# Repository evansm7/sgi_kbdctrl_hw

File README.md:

# SGI Indigo PS/2 keyboard/mouse adapter PCB

26 April 2026

This is the PCB companion to the [sgi_indigo_kbdctrl firmware](https://github.com/evansm7/sgi_indigo_kbdctrl) project. 

Has enough on board to be self-powered using the 8V from the Indigo, or can be built with a barrel jack to take 5VDC (which is probably nicer for the SGI).

Can be built with a dual/stacked PS/2 connector for keyboard/mouse in one footprint, or two one-socket connectors side by side.

# License

sgi_kbdctrl_hw is copyright 2016 Matt Evans.

This work is licensed under the Creative Commons Attribution-NonCommercial-ShareAlike 3.0 Unported License. To view a copy of this license, visit http://creativecommons.org/licenses/by-nc-sa/3.0/ or send a letter to Creative Commons, PO Box 1866, Mountain View, CA 94042, USA.

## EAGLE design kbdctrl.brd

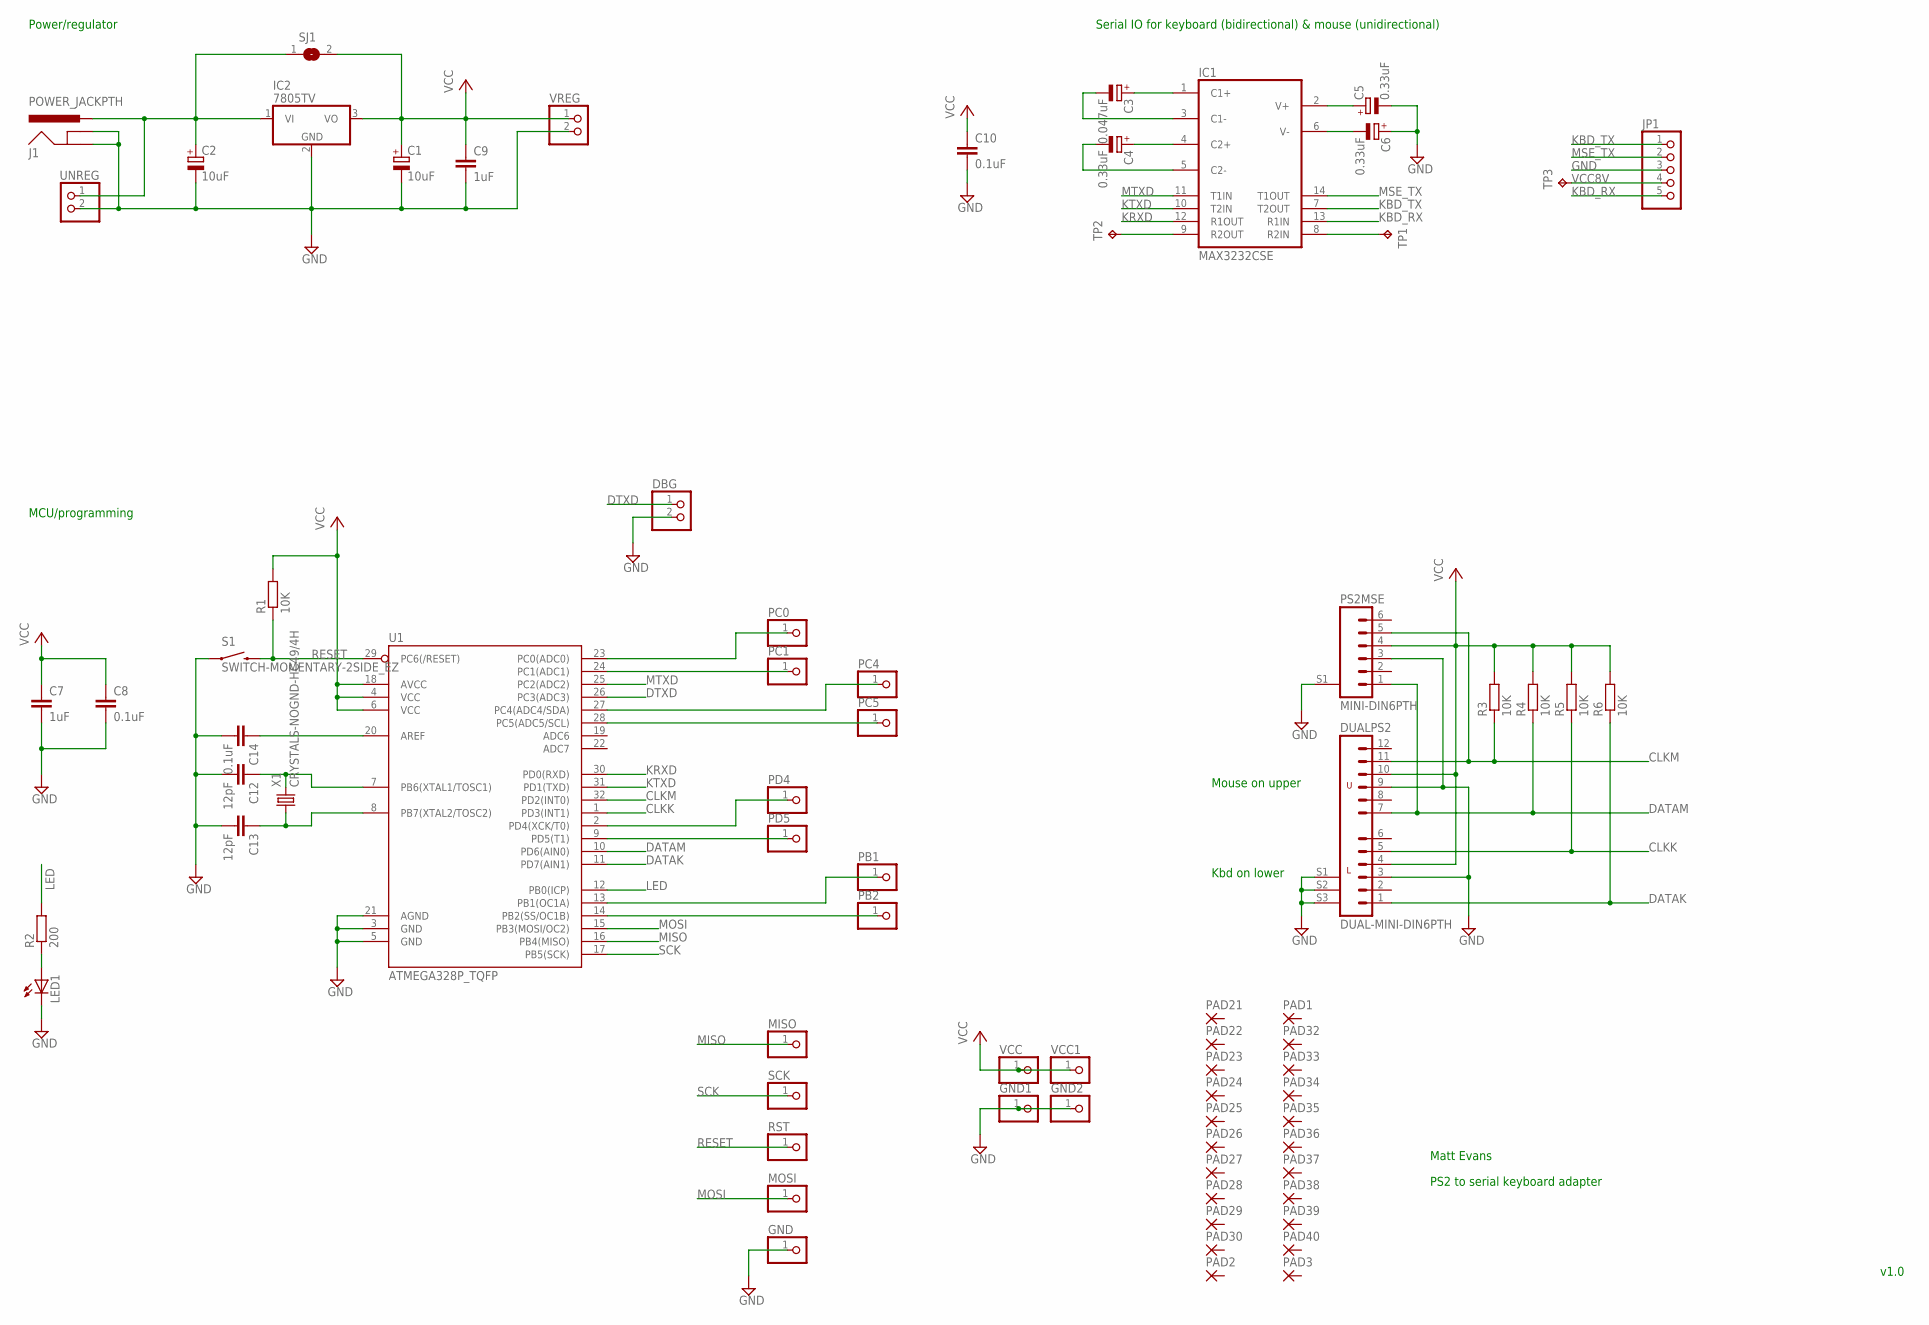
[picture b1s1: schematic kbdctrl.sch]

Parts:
C1, C2: 10uF; SMC_P
C3: 0.047uF; SMC_P
C4, C5, C6: 0.33uF; SMC_P
C7, C9: 1uF; C0805
C8, C10: 0.1uF; C0805
C12, C13: 12pF; C0603
C14: 0.1uF; C0603
DBG: PINHD-1X2; 1X02
DUALPS2: DUAL-MINI-DIN6PTH; DUAL-MINI-DIN6
GND, GND1, GND2: PINHD-1X1; 1X01
IC1: MAX3232CSE; SO16
IC2: 7805TV; TO220V
J1: POWER_JACKPTH; POWER_JACK_PTH
JP1: PINHD-1X5; 1X05
LED1: LEDSML0805; SML0805
MISO: PINHD-1X1; 1X01
MOSI: PINHD-1X1; 1X01
PAD1, PAD2, PAD3, PAD21, PAD22, PAD23, PAD24, PAD25, PAD26, PAD27, PAD28, PAD29, PAD30, PAD32, PAD33, PAD34, PAD35, PAD36, PAD37, PAD38, PAD39, PAD40: 1,6/0,9
PB1, PB2: PINHD-1X1; 1X01
PC0, PC1, PC4, PC5: PINHD-1X1; 1X01
PD4, PD5: PINHD-1X1; 1X01
PS2MSE: MINI-DIN6PTH; MINI-DIN6
R1, R3, R4, R5, R6: 10K; R0603
R2: 200; R0603
RST: PINHD-1X1; 1X01
S1: SWITCH-MOMENTARY-2SIDE_EZ; TACTILE-PTH-SIDEEZ
SCK: PINHD-1X1; 1X01
SJ1: SJ
TP1, TP2, TP3: TPTP09SQ; TP09SQ
U1: ATMEGA328P_TQFP; TQFP32-08
UNREG: PINHD-1X2; 1X02
VCC, VCC1: PINHD-1X1; 1X01
VREG: PINHD-1X2; 1X02
X1: CRYSTALS-NOGND-HC49/4H; HC49

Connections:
CLKK: DUALPS2.5, R5.1, U1.1 (PD3(INT1))
CLKM: DUALPS2.11, PS2MSE.5, R3.1, U1.32 (PD2(INT0))
DATAK: DUALPS2.1, R6.1, U1.11 (PD7(AIN1))
DATAM: DUALPS2.7, PS2MSE.1, R4.1, U1.10 (PD6(AIN0))
DTXD: DBG.1, U1.26 (PC3(ADC3))
GND: C1.-, C2.-, C5.-, C6.+, C7.2, C8.2, C9.2, C10.2, C12.2, C13.2, C14.2, DBG.2, DUALPS2.3, DUALPS2.9, DUALPS2.S1, DUALPS2.S2, DUALPS2.S3, GND.1, GND1.1, GND2.1, IC1.15 (GND), IC2.2 (GND), J1.GND, J1.GNDBREAK, JP1.3, LED1.C, PS2MSE.3, PS2MSE.S1, S1.1, U1.3 (GND), U1.5 (GND), U1.21 (AGND), UNREG.2, VREG.2
KBD_RX: IC1.13 (R1IN), JP1.5
KBD_TX: IC1.7 (T2OUT), JP1.1
KRXD: IC1.12 (R1OUT), U1.30 (PD0(RXD))
KTXD: IC1.10 (T2IN), U1.31 (PD1(TXD))
LED: R2.2, U1.12 (PB0(ICP))
MISO: MISO.1, U1.16 (PB4(MISO))
MOSI: MOSI.1, U1.15 (PB3(MOSI/OC2))
MSE_TX: IC1.14 (T1OUT), JP1.2
MTXD: IC1.11 (T1IN), U1.25 (PC2(ADC2))
unnamed: C3.-, IC1.3 (C1-)
unnamed: C4.+, IC1.4 (C2+)
unnamed: C12.1, U1.7 (PB6(XTAL1/TOSC1)), X1.2
unnamed: C13.1, U1.8 (PB7(XTAL2/TOSC2)), X1.1
unnamed: C4.-, IC1.5 (C2-)
unnamed: C2.+, IC2.1 (VI), J1.PWR, SJ1.1, UNREG.1
unnamed: C14.1, U1.20 (AREF)
unnamed: C3.+, IC1.1 (C1+)
unnamed: C5.+, IC1.2 (V+)
unnamed: C6.-, IC1.6 (V-)
unnamed: IC1.9 (R2OUT), TP2.TP
unnamed: IC1.8 (R2IN), TP1.TP
unnamed: LED1.A, R2.1
unnamed: PB1.1, U1.13 (PB1(OC1A))
unnamed: PD5.1, U1.9 (PD5(T1))
unnamed: PD4.1, U1.2 (PD4(XCK/T0))
unnamed: PC5.1, U1.28 (PC5(ADC5/SCL))
unnamed: PC1.1, U1.24 (PC1(ADC1))
unnamed: PC0.1, U1.23 (PC0(ADC0))
PB2: PB2.1, U1.14 (PB2(SS/OC1B))
PC4: PC4.1, U1.27 (PC4(ADC4/SDA))
RESET: R1.1, RST.1, S1.2, U1.29 (PC6(/RESET))
SCK: SCK.1, U1.17 (PB5(SCK))
VCC: C1.+, C7.1, C8.1, C9.1, C10.1, DUALPS2.4, DUALPS2.10, IC1.16 (VCC), IC2.3 (VO), PS2MSE.4, R1.2, R3.2, R4.2, R5.2, R6.2, SJ1.2, U1.4 (VCC), U1.6 (VCC), U1.18 (AVCC), VCC.1, VCC1.1, VREG.1
VCC8V: JP1.4, TP3.TP

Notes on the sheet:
Matt Evans
PS2 to serial keyboard adapter
Kbd on lower
Mouse on upper
Serial IO for keyboard (bidirectional) & mouse (unidirectional)
Power/regulator
MCU/programming
v1.0

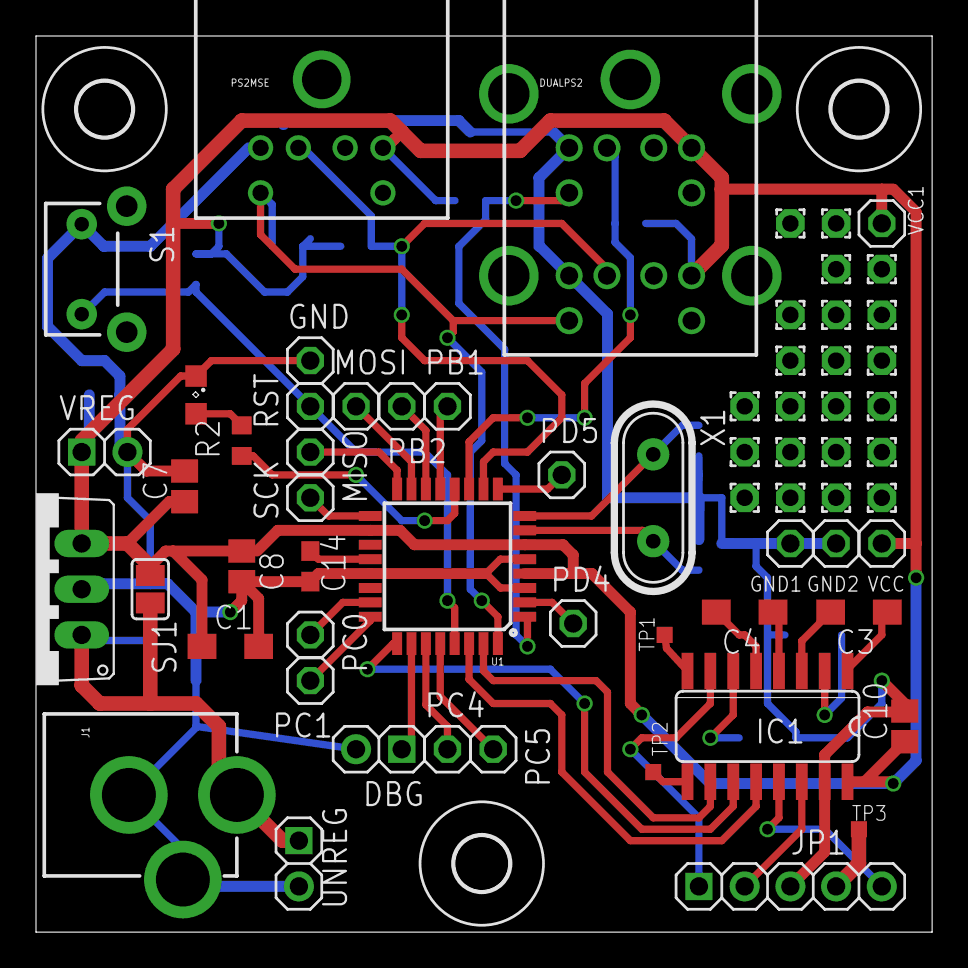
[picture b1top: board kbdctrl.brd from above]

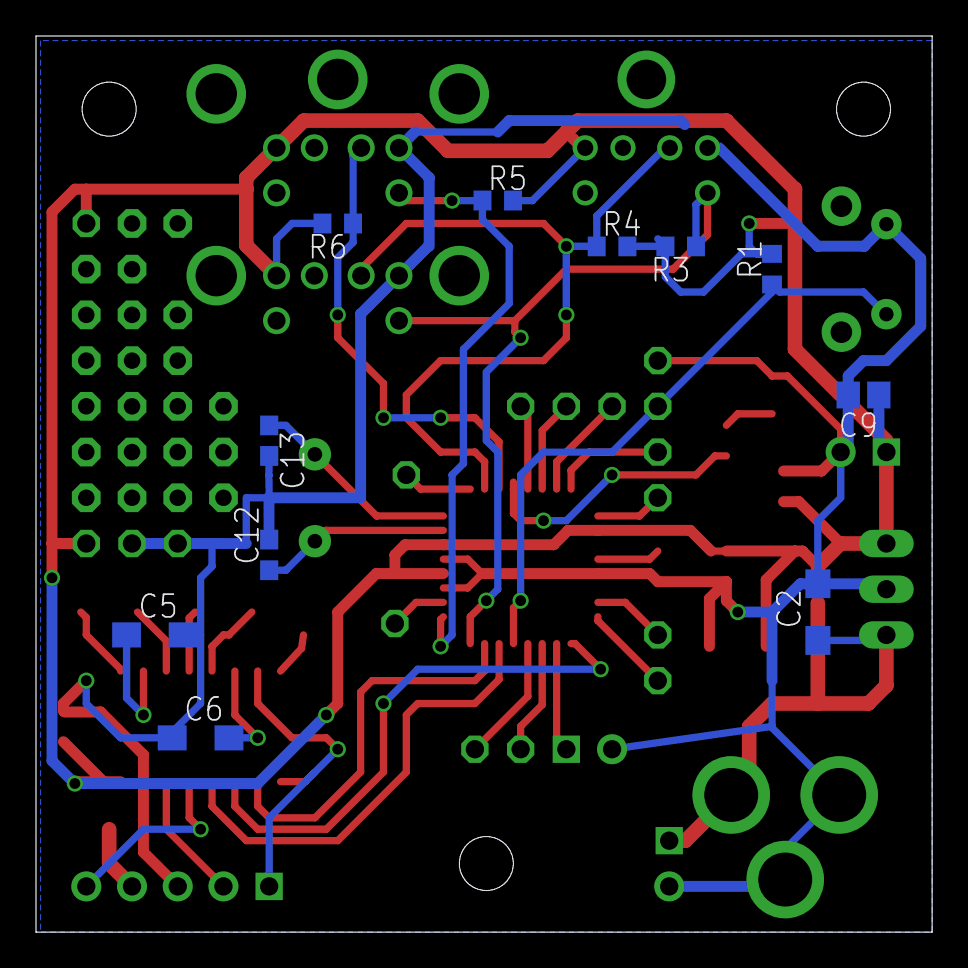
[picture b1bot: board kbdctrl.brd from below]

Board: 2 copper layers, 49.8 x 49.8 mm, 78 parts (11 on the bottom side), 40 nets.

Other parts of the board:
U$2, U$3, U$4: 3,0

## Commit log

2026-04-26 Initial commit for release

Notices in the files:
parts and their libraries:
SparkFun-DigitalIC: Licensing: Creative Commons ShareAlike 4.0 International - https://creativecommons.org/licenses/by-sa/4.0
